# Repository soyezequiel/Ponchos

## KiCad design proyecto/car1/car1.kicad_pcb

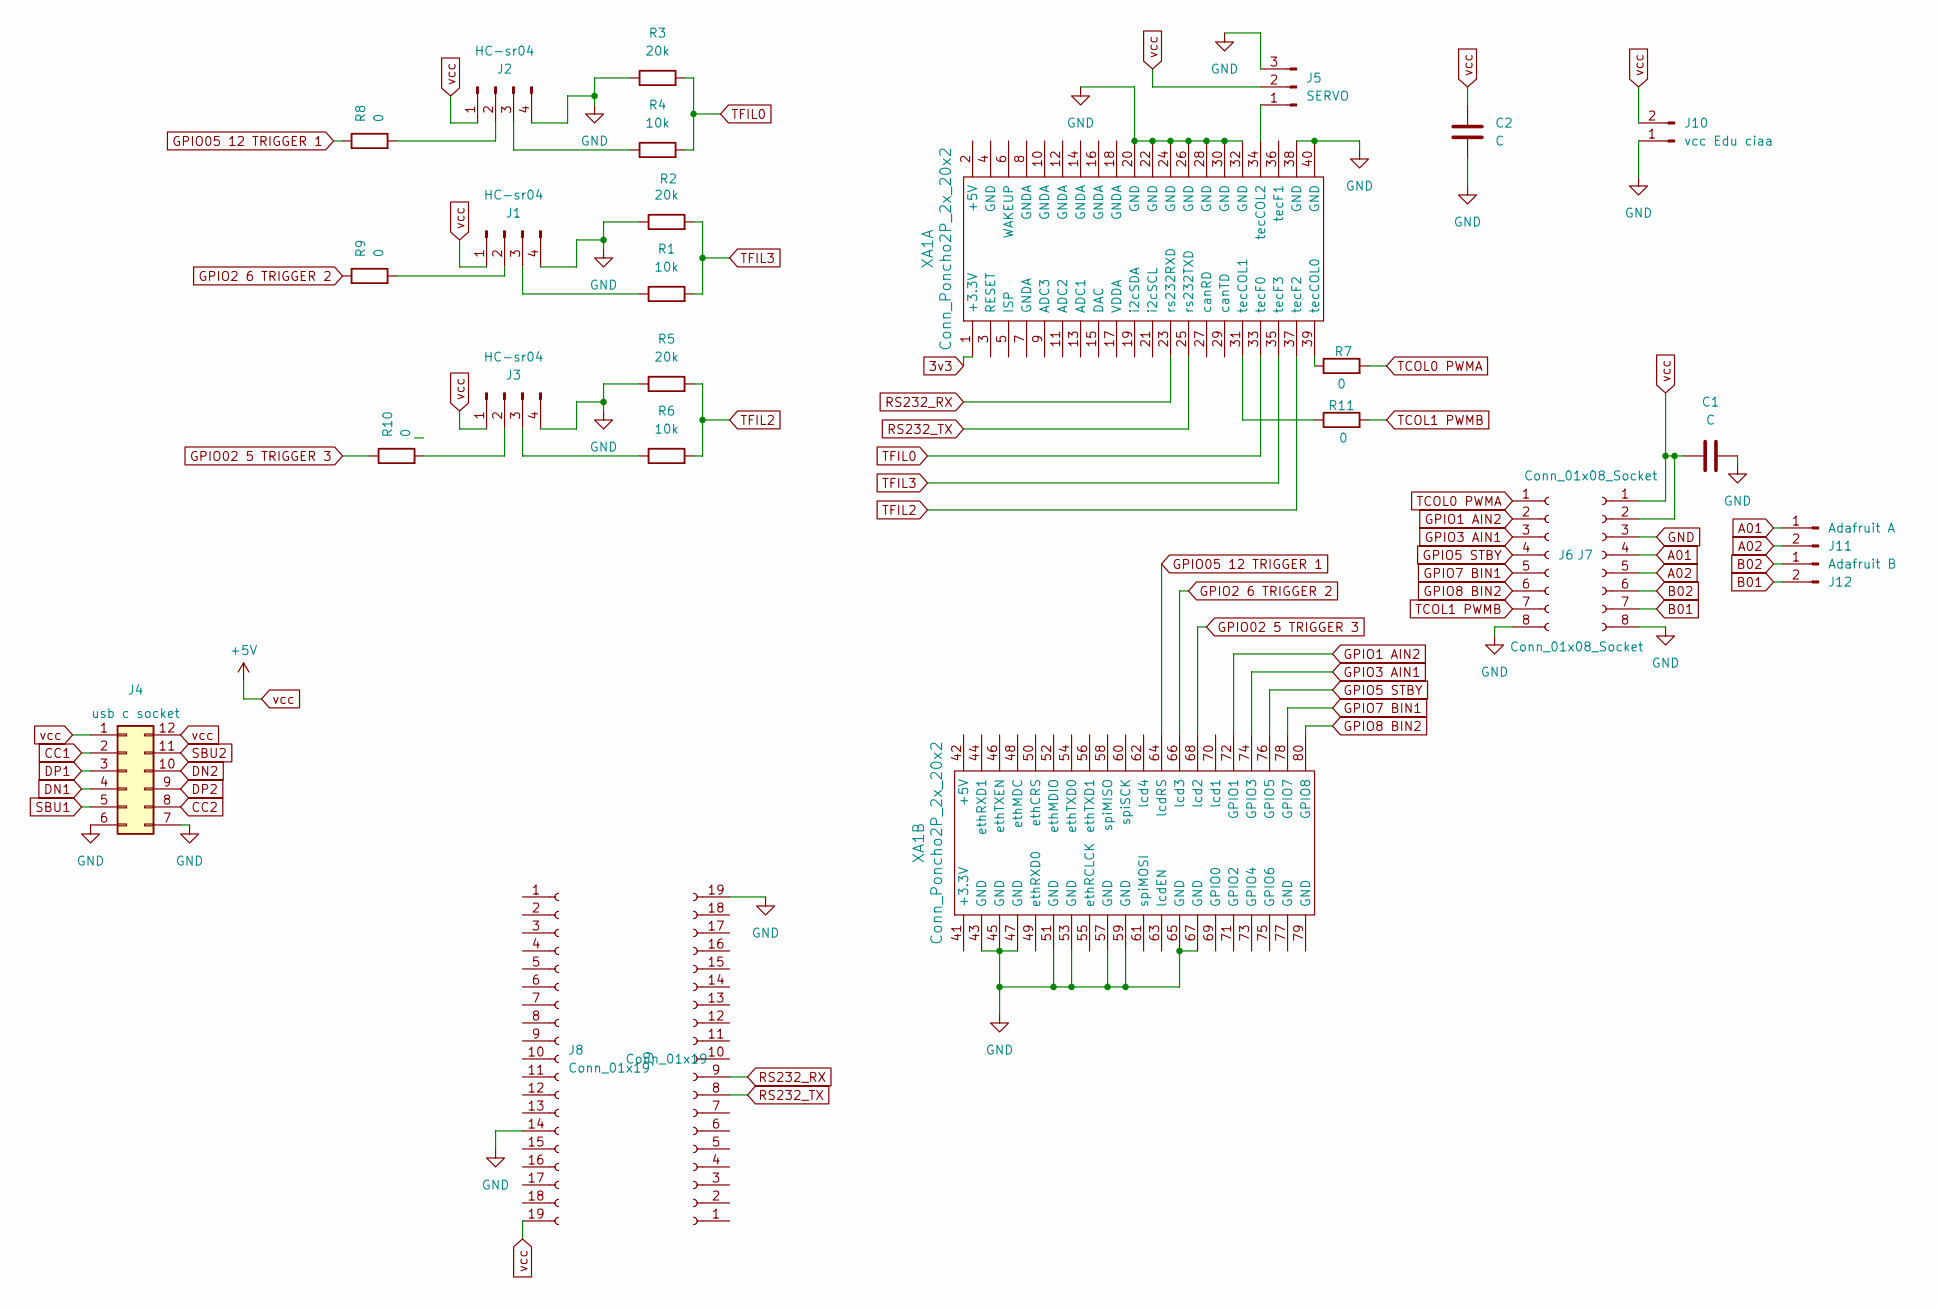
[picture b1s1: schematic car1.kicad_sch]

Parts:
C1, C2: C; C_1206_3216Metric_Pad1.33x1.80mm_HandSolder
J1, J2, J3: HC-sr04; Molex_KK-254_AE-6410-04A_1x04_P2.54mm_Vertical
J4: usb c socket; PinSocket_2x06_P2.54mm_Vertical
J5: SERVO; Molex_KK-254_AE-6410-03A_1x03_P2.54mm_Vertical
J6, J7: Conn_01x08_Socket; PinSocket_1x08_P2.54mm_Vertical
J8, J9: Conn_01x19; PinSocket_1x19_P2.54mm_Vertical
J10: vcc Edu ciaa; Molex_KK-254_AE-6410-02A_1x02_P2.54mm_Vertical
J11: Adafruit A; Molex_KK-254_AE-6410-02A_1x02_P2.54mm_Vertical
J12: Adafruit B; Molex_KK-254_AE-6410-02A_1x02_P2.54mm_Vertical
R1, R4, R6: 10k; R_1206_3216Metric_Pad1.30x1.75mm_HandSolder
R2, R3, R5: 20k; R_1206_3216Metric_Pad1.30x1.75mm_HandSolder
R7, R8, R9, R10, R11: 0; R_Axial_DIN0207_L6.3mm_D2.5mm_P10.16mm_Horizontal
XA1: Conn_Poncho2P_2x_20x2; Conn_Poncho_SinBorde

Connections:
3v3: XA1.1 (+3.3V)
A01: J7.4, J11.1
A02: J7.5, J11.2
B01: J7.7, J12.2
B02: J7.6, J12.1
CC1: J4.2
CC2: J4.8
DN1: J4.4
DN2: J4.10
DP1: J4.3
DP2: J4.9
GND: C1.2, C2.1, J1.4 (GND), J2.4 (GND), J3.4 (GND), J4.6, J4.7, J5.3 (señal), J6.8, J7.3, J7.8, J8.14, J9.19, J10.1, R2.1, R3.1, R5.1, XA1.20 (GND), XA1.22 (GND), XA1.24 (GND), XA1.26 (GND), XA1.28 (GND), XA1.30 (GND), XA1.32 (GND), XA1.38 (GND), XA1.40 (GND), XA1.43 (GND), XA1.45 (GND), XA1.47 (GND), XA1.51 (GND), XA1.53 (GND), XA1.57 (GND), XA1.59 (GND), XA1.65 (GND), XA1.67 (GND)
GPIO1 AIN2: J6.2, XA1.72 (GPIO1)
GPIO02 5 TRIGGER 3: R10.1, XA1.68 (lcd2)
GPIO2 6 TRIGGER 2: R9.1, XA1.66 (lcd3)
GPIO3 AIN1: J6.3, XA1.74 (GPIO3)
GPIO05 12 TRIGGER 1: R8.1, XA1.64 (lcdRS)
GPIO5 STBY: J6.4, XA1.76 (GPIO5)
GPIO7 BIN1: J6.5, XA1.78 (GPIO7)
GPIO8 BIN2: J6.6, XA1.80 (GPIO8)
unnamed: J1.3 (ECHO), R1.1
unnamed: J1.2 (trigger), R9.2
unnamed: J2.3 (ECHO), R4.1
unnamed: J2.2 (trigger), R8.2
unnamed: J3.3 (ECHO), R6.1
unnamed: J3.2 (trigger), R10.2
unnamed: J5.1 (GNC), XA1.34 (tecCOL2)
unnamed: R7.1, XA1.39 (tecCOL0)
unnamed: R11.1, XA1.31 (tecCOL1)
RS232_RX: J9.9, XA1.23 (rs232RXD)
RS232_TX: J9.8, XA1.25 (rs232TXD)
SBU1: J4.5
SBU2: J4.11
TCOL0 PWMA: J6.1, R7.2
TCOL1 PWMB: J6.7, R11.2
TFIL0: R3.2, R4.2, XA1.33 (tecF0)
TFIL2: R5.2, R6.2, XA1.37 (tecF2)
TFIL3: R1.2, R2.2, XA1.35 (tecF3)
vcc: C1.1, C2.2, J1.1 (5v), J2.1 (5v), J3.1 (5v), J4.1, J4.12, J5.2 (VIN), J7.1, J7.2, J8.19, J10.2

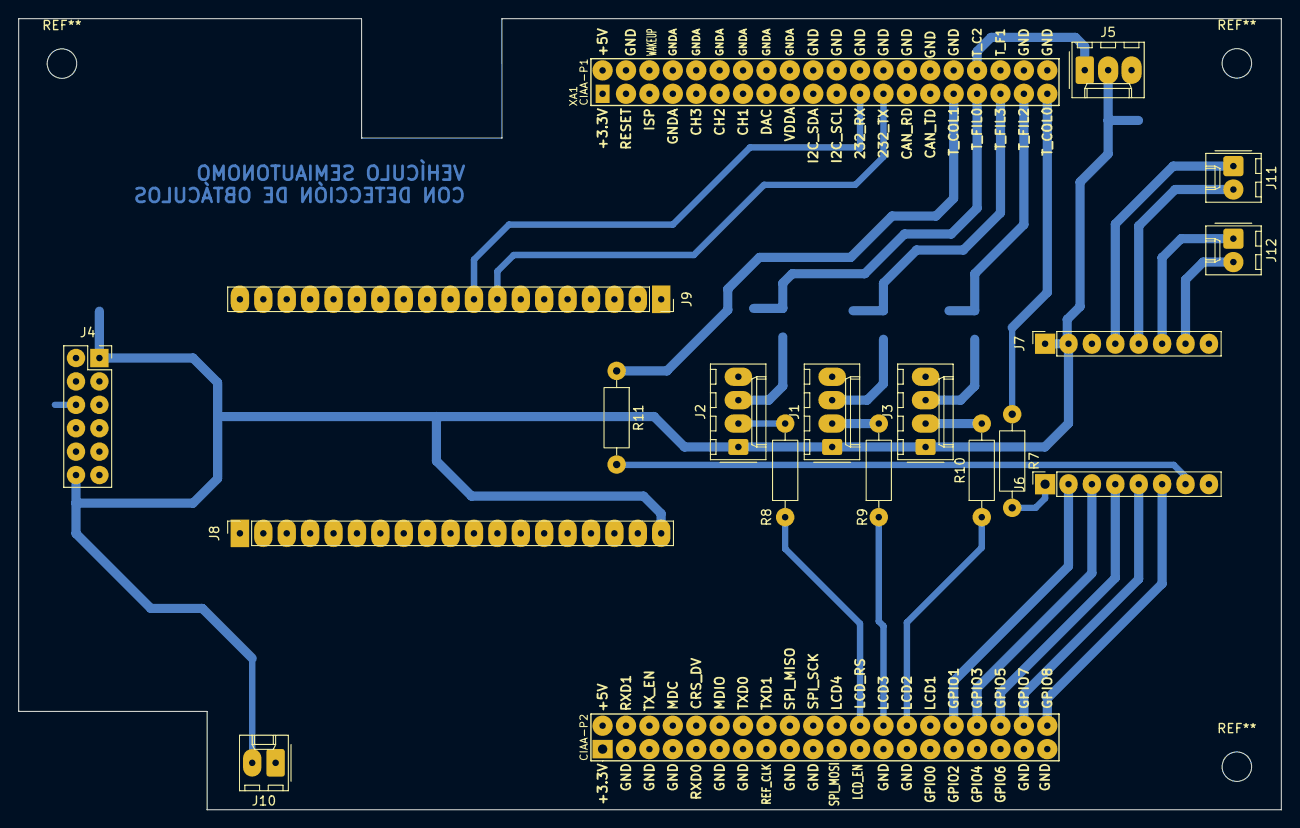
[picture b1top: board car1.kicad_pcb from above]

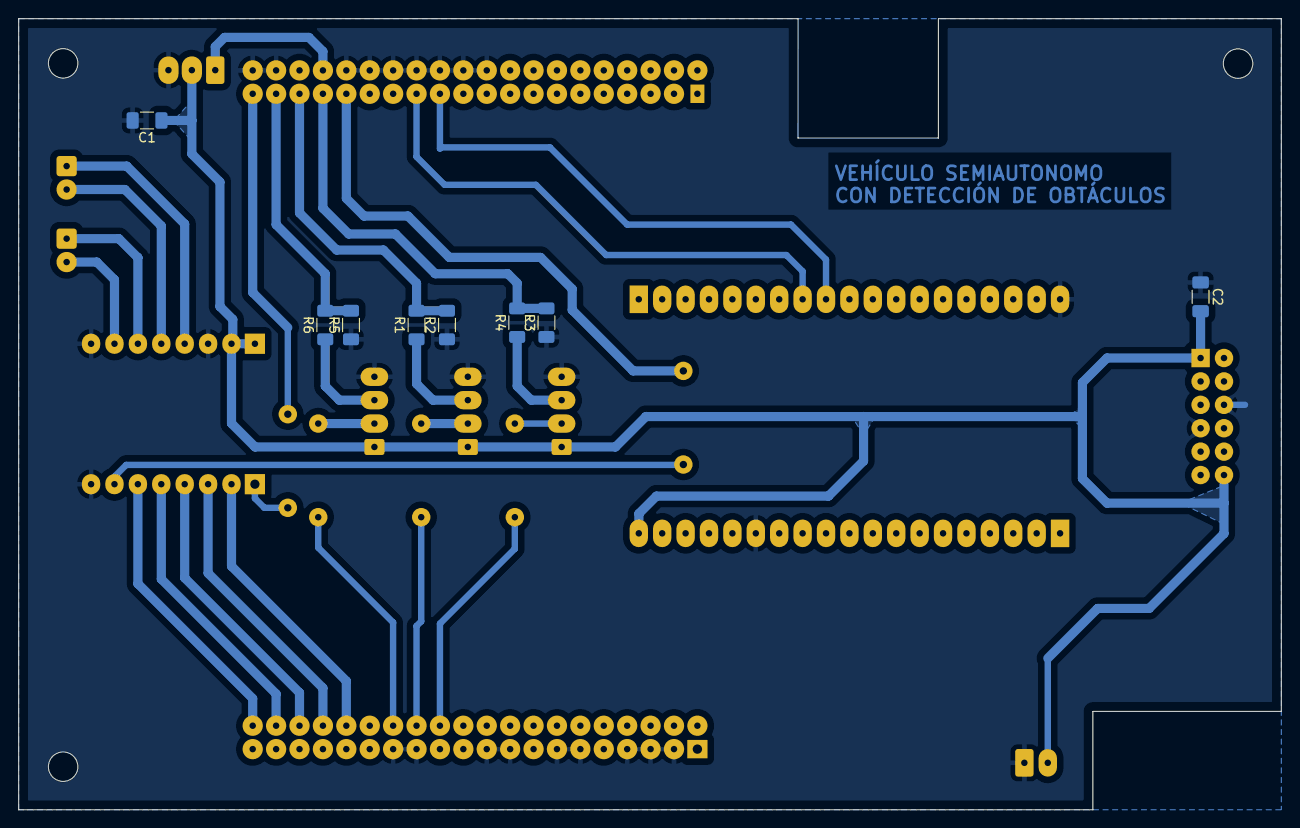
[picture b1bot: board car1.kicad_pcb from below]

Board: 2 copper layers, 137.0 x 85.9 mm, 26 parts (8 on the bottom side), 30 nets.

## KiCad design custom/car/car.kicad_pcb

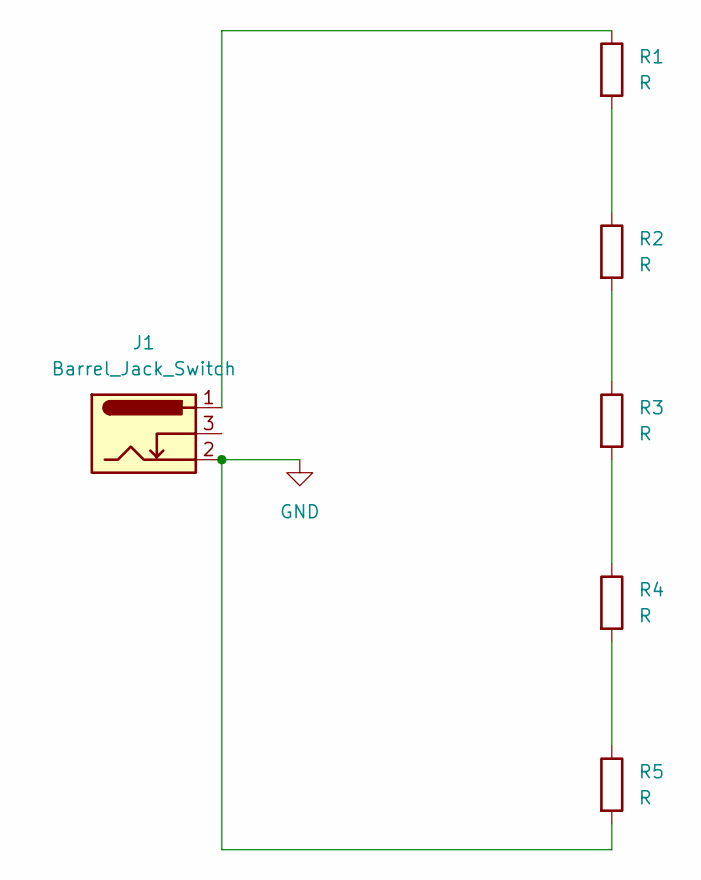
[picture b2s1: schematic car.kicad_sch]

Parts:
J1: Barrel_Jack_Switch; BarrelJack_Kycon_KLDX-0202-xC_Horizontal
R1, R2, R3, R4, R5: R; R_Axial_DIN0617_L17.0mm_D6.0mm_P25.40mm_Horizontal

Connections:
GND: J1.2, R5.2
unnamed: J1.1, R1.1
unnamed: R1.2, R2.1
unnamed: R2.2, R3.1
unnamed: R3.2, R4.1
unnamed: R4.2, R5.1

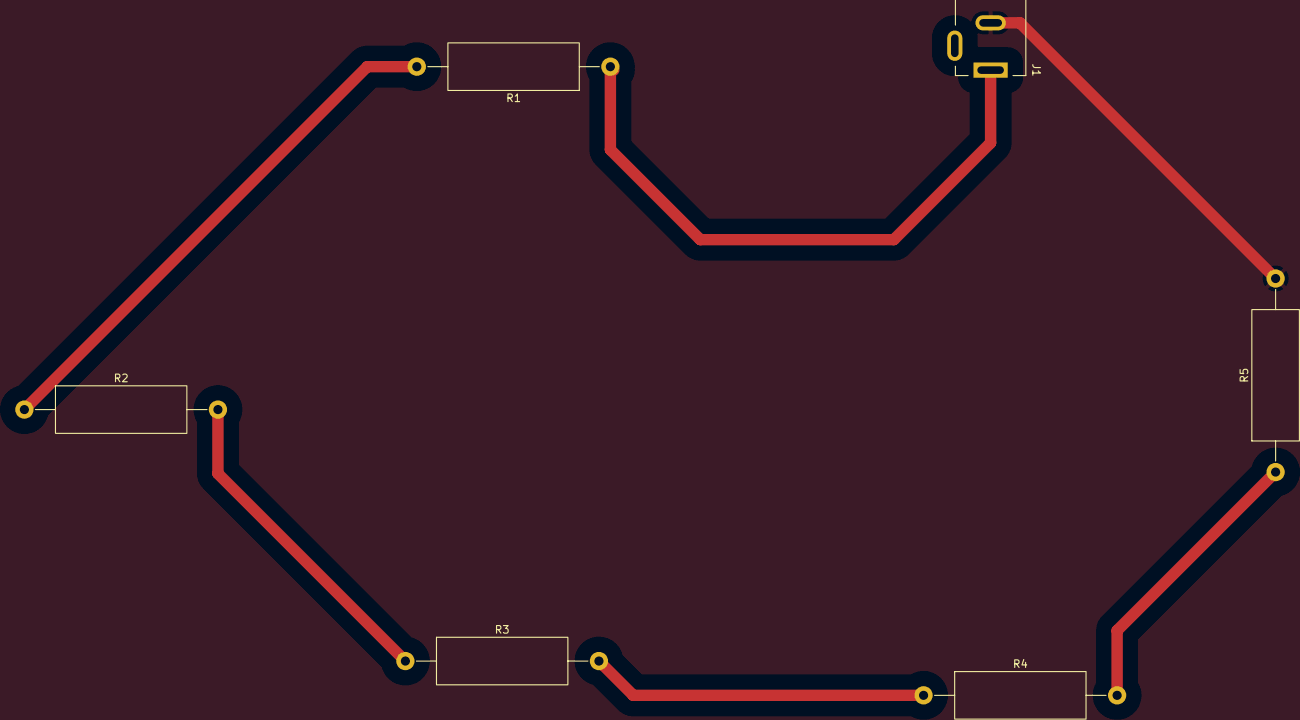
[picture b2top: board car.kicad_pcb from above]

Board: 2 copper layers, 6 parts (0 on the bottom side), 6 nets.

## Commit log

2025-10-21 commit inicial
2025-10-21 se agregaron los componentes
2025-10-21 se agregaron todos los componentes
2025-10-22 creacion de conexiones
2025-10-23 ultima version del poncho
2025-10-27 cambio de pines
2025-10-27 cambios de esquina de poncho
2025-10-28 cambios mayores
2025-10-30 arreglos menores
2025-10-30 fix esp32
2025-11-11 giga pad
2025-11-11 fix pista
